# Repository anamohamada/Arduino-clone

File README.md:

# Arduino-clone
An Arduino clone
Thsi is my first PCB project using Kicad, 
Thanks to Dr. Peter Dalmaris 
Educator and Author of "Maker Education Revolution"

I did Not manufacture the PCB yet.

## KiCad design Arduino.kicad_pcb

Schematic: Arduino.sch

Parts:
BT1: Battery 3V; PinHeader_1x02_P2.54mm_Vertical
C1, C2: 22pF; C_0805_2012Metric_Pad1.18x1.45mm_HandSolder
C3: 10uF; C_0805_2012Metric_Pad1.18x1.45mm_HandSolder
D1: LED; LED_0805_2012Metric_Pad1.15x1.40mm_HandSolder
R1: 330 ohm; R_0805_2012Metric_Pad1.20x1.40mm_HandSolder
R2: 10K ohm; R_0805_2012Metric_Pad1.20x1.40mm_HandSolder
U1: DS1337_AH; SO-8_5.3x6.2mm_P1.27mm
U2, U3: 24LC1025; SOIC-8_5.23x5.23mm_P1.27mm
U4: ATMEGA328P-AU; TQFP-32_7x7mm; MPN ATMEGA328P-AU; Digi-Key_PN ATMEGA328P-AU-ND
Y1: Crystal 32MHZ; Crystal_SMD_MicroCrystal_CC7V-T1A-2Pin_3.2x1.5mm
Y2: Crystal 16MHZ; Crystal_SMD_5032-2Pin_5.0x3.2mm_HandSoldering

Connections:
/ADDS1: U2.1 (A0), U3.1 (A0), U4.23 (PC0)
/ADDS2: U2.2 (A1), U3.2 (A1), U4.24 (PC1)
/D2: U4.32 (PD2); also elsewhere on the board
/D3: U4.1 (PD3); also elsewhere on the board
/D4: U4.2 (PD4); also elsewhere on the board
/D5: U4.9 (PD5); also elsewhere on the board
/D6: U4.10 (PD6); also elsewhere on the board
/D7: U4.11 (PD7); also elsewhere on the board
/D8: U4.12 (PB0); also elsewhere on the board
/MISO: U4.16 (PB4); also elsewhere on the board
/MOSI: U4.15 (PB3); also elsewhere on the board
/RESET: R2.1, U4.29 (PC6); also elsewhere on the board
/RX: U4.30 (PD0); also elsewhere on the board
/SCK: D1.2 (A), U4.17 (PB5); also elsewhere on the board
/SCL: U1.6 (SCL), U2.6 (SCL), U3.6 (SCL), U4.28 (PC5)
/SDA: U1.5 (SDA), U2.5 (SDA), U3.5 (SDA), U4.27 (PC4); also elsewhere on the board
/TX: U4.31 (PD1); also elsewhere on the board
/VCC: BT1.1 (+), C3.1, R2.2, U1.3 (INTA), U1.8 (Vcc), U2.3 (A2), U2.8 (VCC), U3.3 (A2), U3.8 (VCC), U4.4 (VCC), U4.6 (VCC), U4.18 (AVCC), U4.20 (AREF); also elsewhere on the board
GNDPWR: BT1.2 (-), C1.2, C2.2, C3.2, R1.2, U1.4 (GND), U2.4 (GND), U2.7 (WP), U3.4 (GND), U3.7 (WP), U4.3 (GND), U4.5 (GND), U4.21 (GND); also elsewhere on the board
unnamed: C1.1, U4.8 (PB7), Y2.1
unnamed: C2.1, U4.7 (PB6), Y2.2
unnamed: D1.1 (K), R1.1
unnamed: U1.1 (X1), Y1.1
unnamed: U1.2 (X2), Y1.2

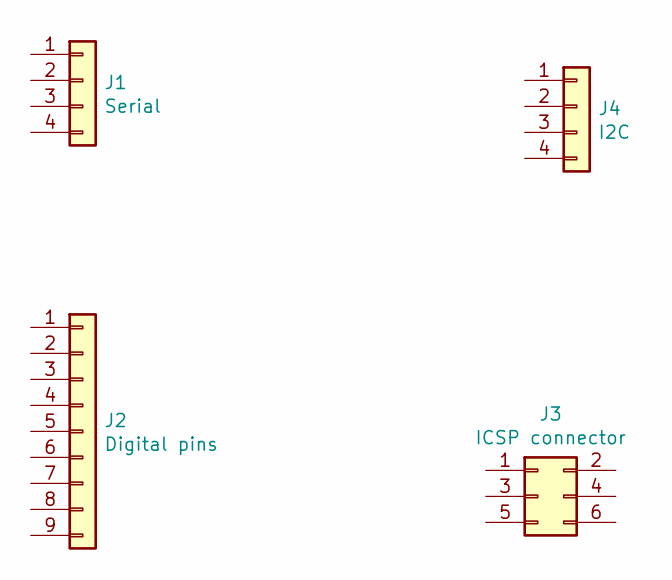
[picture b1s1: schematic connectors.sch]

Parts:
J1: Serial; PinSocket_1x04_P2.54mm_Vertical
J2: Digital pins; PinSocket_1x09_P2.54mm_Vertical
J3: ICSP connector; PinSocket_2x03_P2.54mm_Vertical
J4: I2C; PinSocket_1x04_P2.54mm_Vertical

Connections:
/D2: J2.1; also elsewhere on the board
/D3: J2.2; also elsewhere on the board
/D4: J2.3; also elsewhere on the board
/D5: J2.4; also elsewhere on the board
/D6: J2.5; also elsewhere on the board
/D7: J2.6; also elsewhere on the board
/D8: J2.7; also elsewhere on the board
/MISO: J3.1; also elsewhere on the board
/MOSI: J3.4; also elsewhere on the board
/RESET: J3.5; also elsewhere on the board
/RX: J1.3; also elsewhere on the board
/SCK: J3.3, J4.4; also elsewhere on the board
/SDA: J4.3; also elsewhere on the board
/TX: J1.4; also elsewhere on the board
/VCC: J1.2, J2.9, J3.2, J4.2; also elsewhere on the board
GNDPWR: J1.1, J2.8, J3.6, J4.1; also elsewhere on the board

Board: 2 copper layers, 17 parts (0 on the bottom side), 24 nets, no tracks yet.

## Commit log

2021-10-07 start
2021-10-07 The project has started
2021-10-07 Add projects simples and adding a sun Sch
2021-10-07 Add a new symbol library DS1337_AH to Ahmad library
2021-10-07 Complete the association with footprint
2021-10-08 Completed the connection in the connectors sheet
2021-10-08 Generate a netList
2021-10-08 Set desighn rules
2021-10-09 Complete the placement
2021-10-09 add an auto routing path tp the project
2021-10-09 Adding a filling layer to the 2 layer kicad_pcb
